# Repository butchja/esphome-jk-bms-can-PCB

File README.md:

It is recommended to reflow solder with solder paste and stencil. 

Features
- small single board solution
- CAN is now 5V as required by standard
- power supply is compatible to battery voltages now

Materials required
- antenna cable: MHF3 to RP-SMA breakout cable 7cm
- wifi antenna
- BMC cable: JST XH 2.5mm - JST SH 1.25mm
- 2pcs M5 nuts
- 2pc M5x10 screws
- 4pcs M3x5 threaded inserts
- 4pcs M3x6 screws

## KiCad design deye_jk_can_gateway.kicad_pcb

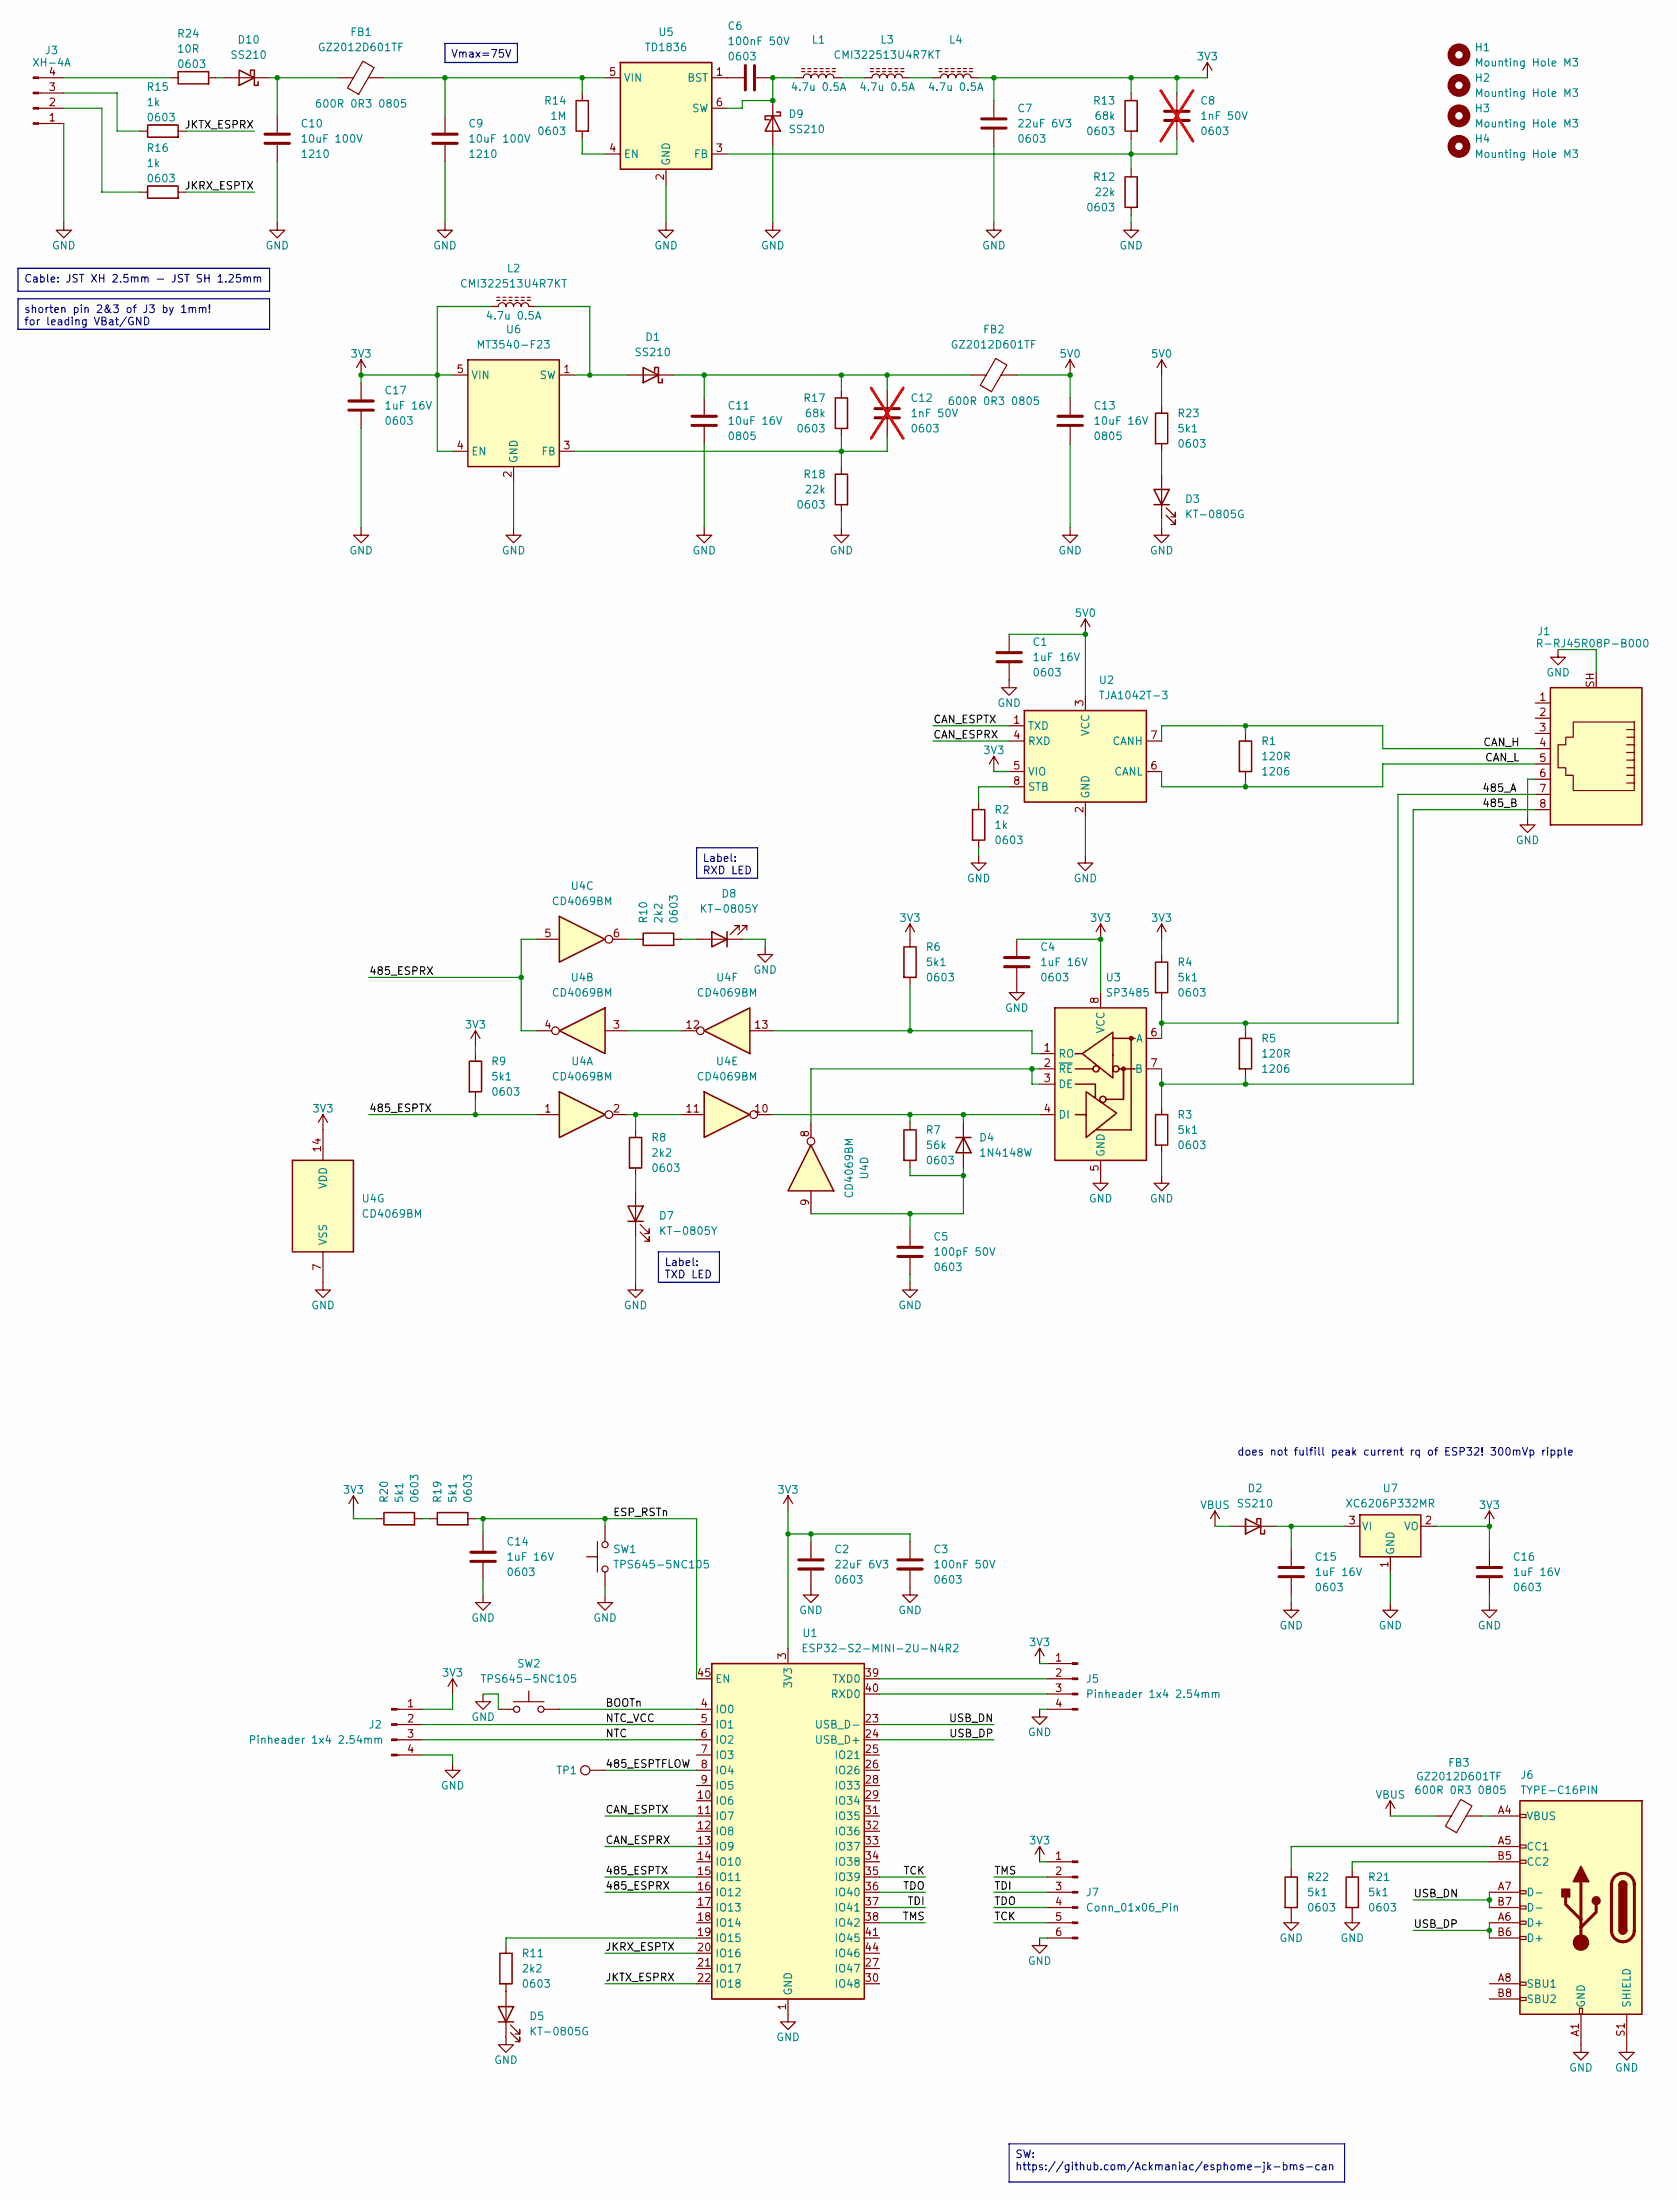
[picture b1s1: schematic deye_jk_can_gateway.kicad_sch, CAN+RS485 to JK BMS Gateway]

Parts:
C1, C4, C14, C15, C16, C17: 1uF 16V; C_0603_1608Metric; LCSC C1592
C2, C7: 22uF 6V3; C_0603_1608Metric; LCSC C59461
C3, C6: 100nF 50V; C_0603_1608Metric; LCSC C1591
C5: 100pF 50V; C_0603_1608Metric; LCSC C14858
C8, C12: 1nF 50V; C_0603_1608Metric; LCSC C1588; not fitted
C9, C10: 10uF 100V; C_1210_3225Metric; LCSC C576517
C11, C13: 10uF 16V; C_0805_2012Metric; LCSC C1713
D1, D9: SS210; D_SMA
D2, D10: SS210; D_SMA; LCSC C14996
D3, D5: KT-0805G; LED_0805_2012Metric; LCSC C2297
D4: 1N4148W; D_SOD-123; LCSC C2099
D7, D8: KT-0805Y; LED_0805_2012Metric; LCSC C2296
FB1, FB2, FB3: GZ2012D601TF; L_0805_2012Metric; LCSC C1017
H1, H2, H3, H4: Mounting Hole M3; MountingHole_3.2mm_M3_ISO7380
J1: R-RJ45R08P-B000; RJ45_Amphenol_RJHSE5380; LCSC C386756
J2, J5: Pinheader 1x4 2.54mm; PinHeader_1x04_P2.54mm_Vertical
J3: XH-4A; JST_XH_B4B-XH-A_1x04_P2.50mm_Vertical
J6: TYPE-C16PIN; USB_C_Receptacle_GCT_USB4105-xx-A_16P_TopMnt_Horizontal; LCSC C393939
J7: Conn_01x06_Pin; PinHeader_1x06_P2.54mm_Vertical
L1, L2, L3, L4: CMI322513U4R7KT; L_1210_3225Metric; LCSC C60534
R1, R5: 120R; R_1206_3216Metric; LCSC C17909
R2, R15, R16: 1k; R_0603_1608Metric; LCSC C21190
R3, R4, R6, R9, R19, R20, R21, R22, R23: 5k1; R_0603_1608Metric; LCSC C23186
R7: 56k; R_0603_1608Metric; LCSC C23206
R8, R10, R11: 2k2; R_0603_1608Metric; LCSC C4190
R12, R18: 22k; R_0603_1608Metric; LCSC C31850
R13, R17: 68k; R_0603_1608Metric; LCSC C23231
R14: 1M; R_0603_1608Metric; LCSC C22935
R24: 10R; R_0603_1608Metric; LCSC C21190
SW1, SW2: TPS645-5NC105; SW_SPST_PTS645; LCSC C19191549
TP1: TestPoint; TestPoint_Pad_1.0x1.0mm
U1: ESP32-S2-MINI-2U-N4R2; ESP32-S2-MINI-1U; LCSC C3013909
U2: TJA1042T-3; SOIC-8_3.9x4.9mm_P1.27mm; LCSC C132227
U3: SP3485; SOIC-8_3.9x4.9mm_P1.27mm; LCSC C8963
U4: CD4069BM; SOIC-14_3.9x8.7mm_P1.27mm; LCSC C22384785
U5: TD1836; SOT-23-6; LCSC C2935198
U6: MT3540-F23; SOT-23-5; LCSC C181783
U7: XC6206P332MR; SOT-23-3; LCSC C5446

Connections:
3V3: C2.1, C3.1, C4.1, C7.1, C8.1, C16.1, C17.1, J2.1, J5.1, J7.1, L2.1, L4.2, R4.1, R6.1, R9.1, R13.1, R20.1, U1.3 (3V3), U2.5 (VIO), U3.8 (VCC), U4.14 (VDD), U6.4 (EN), U6.5 (VIN), U7.2 (VO)
5V0: C1.1, C13.1, FB2.2, R23.1, U2.3 (VCC)
/485_A: J1.7, R4.2, R5.1, U3.6 (A)
/485_B: J1.8, R3.1, R5.2, U3.7 (B)
/485_ESPRX: U1.16 (IO12), U4.4, U4.5
/485_ESPTFLOW: TP1.1, U1.8 (IO4)
/485_ESPTX: R9.2, U1.15 (IO11), U4.1
/BOOTn: SW2.2, U1.4 (IO0)
/CAN_ESPRX: U1.13 (IO9), U2.4 (RXD)
/CAN_ESPTX: U1.11 (IO7), U2.1 (TXD)
/CAN_H: J1.4, R1.1, U2.7 (CANH)
/CAN_L: J1.5, R1.2, U2.6 (CANL)
/ESP_RSTn: C14.1, R19.2, SW1.2, U1.45 (EN)
/JKRX_ESPTX: R16.2, U1.20 (IO16)
/JKTX_ESPRX: R15.2, U1.22 (IO18)
/NTC: J2.3, U1.6 (IO2)
/NTC_VCC: J2.2, U1.5 (IO1)
/TCK: J7.5, U1.35 (IO39)
/TDI: J7.3, U1.37 (IO41)
/TDO: J7.4, U1.36 (IO40)
/TMS: J7.2, U1.38 (IO42)
/USB_DN: J6.A7 (D-), J6.B7 (D-), U1.23 (USB_D-)
/USB_DP: J6.A6 (D+), J6.B6 (D+), U1.24 (USB_D+)
GND: C1.2, C2.2, C3.2, C4.2, C5.2, C7.2, C9.2, C10.2, C11.2, C13.2, C14.2, C15.2, C16.2, C17.2, D3.1 (K), D5.1 (K), D7.1 (K), D8.1 (K), D9.2 (A), J1.6, J1.SH, J2.4, J3.1, J5.4, J6.A1 (GND), J6.A12 (GND), J6.B1 (GND), J6.B12 (GND), J6.S1 (SHIELD), J7.6, R2.2, R3.2, R12.2, R18.2, R21.2, R22.2, SW1.1, SW2.1, U1.1 (GND), U1.2 (GND), U1.42 (GND), U1.43 (GND), U1.46 (GND), U1.47 (GND), U1.48 (GND), U1.49 (GND), U1.50 (GND), U1.51 (GND), U1.52 (GND), U1.53 (GND), U1.54 (GND), U1.55 (GND), U1.56 (GND), U1.57 (GND), U1.58 (GND), U1.59 (GND), U1.60 (GND), U1.61 (GND), U1.62 (GND), U1.63 (GND), U1.64 (GND), U1.65 (GND), U2.2 (GND), U3.5 (GND), U4.7 (VSS), U5.2 (GND), U6.2 (GND), U7.1 (GND)
unnamed: D1.2 (A), L2.2, U6.1 (SW)
unnamed: C11.1, C12.1, D1.1 (K), FB2.1, R17.1
unnamed: C15.1, D2.1 (K), U7.3 (VI)
unnamed: D3.2 (A), R23.2
unnamed: C5.1, D4.2 (A), R7.2, U4.9
unnamed: D4.1 (K), R7.1, U3.4 (DI), U4.10
unnamed: D5.2 (A), R11.2
unnamed: D7.2 (A), R8.2
unnamed: D8.2 (A), R10.2
unnamed: C6.2, D9.1 (K), L1.1, U5.6 (SW)
unnamed: D10.2 (A), R24.2
unnamed: C10.1, D10.1 (K), FB1.1
unnamed: FB3.2, J6.A4 (VBUS), J6.A9 (VBUS), J6.B4 (VBUS), J6.B9 (VBUS)
unnamed: J3.2, R16.1
unnamed: J3.3, R15.1
unnamed: J3.4, R24.1
unnamed: J5.2, U1.39 (TXD0)
unnamed: J5.3, U1.40 (RXD0)
unnamed: J6.A5 (CC1), R22.1
unnamed: J6.B5 (CC2), R21.1
unnamed: L1.2, L3.1
unnamed: L3.2, L4.1
unnamed: R8.1, U4.2, U4.11
unnamed: R10.1, U4.6
unnamed: R19.1, R20.2
unnamed: R11.1, U1.19 (IO15)
unnamed: R2.1, U2.8 (STB)
unnamed: U3.2 (~RE), U3.3 (DE), U4.8
unnamed: R6.2, U3.1 (RO), U4.13
unnamed: U4.3, U4.12
unnamed: C6.1, U5.1 (BST)
unnamed: R14.2, U5.4 (EN)
unnamed: C8.2, R12.1, R13.2, U5.3 (FB)
unnamed: C9.1, FB1.2, R14.1, U5.5 (VIN)
unnamed: C12.2, R17.2, R18.1, U6.3 (FB)
VBUS: D2.2 (A), FB3.1

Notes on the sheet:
does not fulfill peak current rq of ESP32! 300mVp ripple
Label: RXD LED
shorten pin 2&3 of J3 by 1mm! for leading VBat/GND
Label: TXD LED
Cable: JST XH 2.5mm - JST SH 1.25mm
SW: https://github.com/Ackmaniac/esphome-jk-bms-can
Vmax=75V

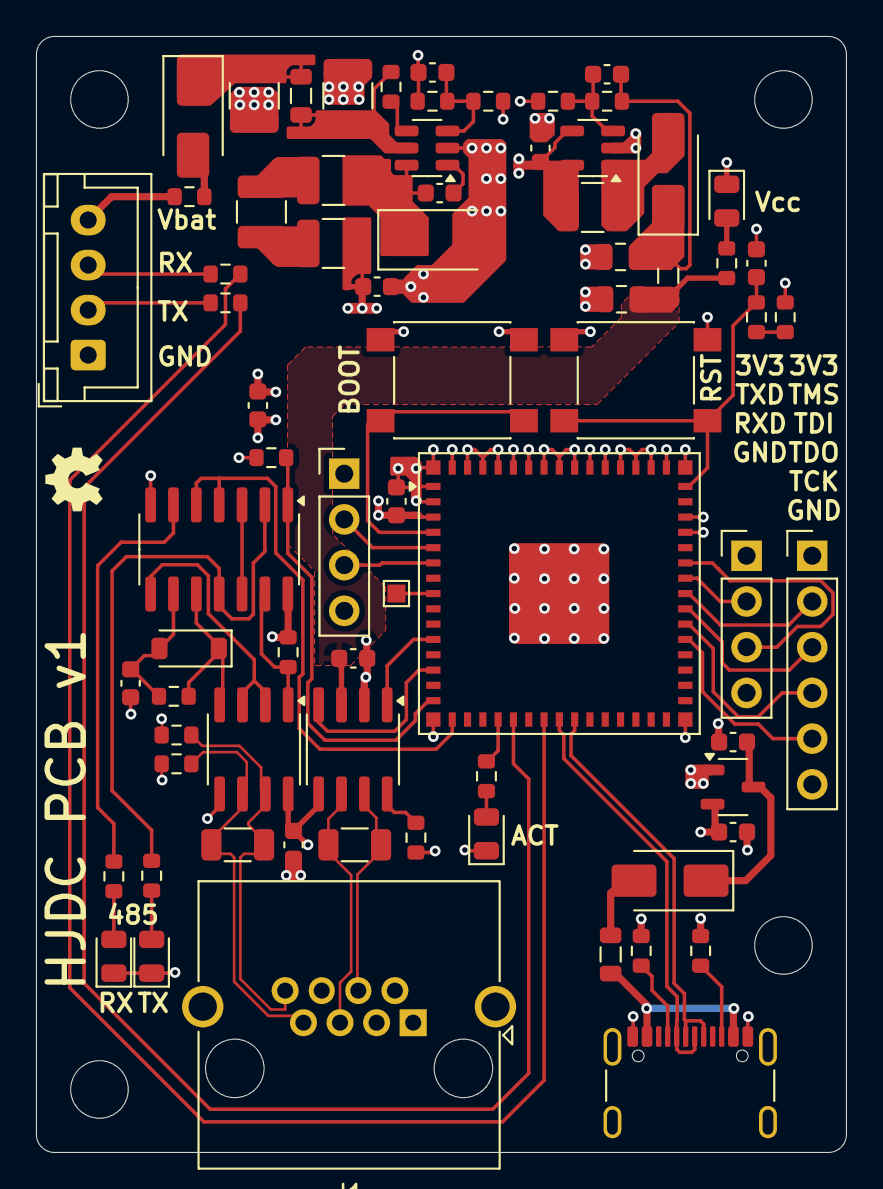
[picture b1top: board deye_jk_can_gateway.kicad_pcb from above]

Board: 4 copper layers, 45.0 x 62.0 mm, 77 parts (0 on the bottom side), 60 nets.

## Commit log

2025-07-05 commit after built successful prototype
    KiCAD project and Design Spark Mechanical PCB Holder.
2025-07-06 filled ground plane
